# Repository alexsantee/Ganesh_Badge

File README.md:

# Ganesh Badge

The board is entirely based on [Ganesh](https://ganesh.icmc.usp.br/)'s logo, the back side has the logo printed in silkscreen and the front side has a circuit part shaped like the logo, which serves as a ground plane. The front also has the names of our main study areas.

The project is based in the PIC10F200 microcontroler, which offers low cost, decent current sourcing and 4 I/O pins.
The PCB features an LED, header pins intended as a serial and a programming interfaces and a button. These are for creating simple CTF-like challenges yielding a flag, being the button a mean of switching which challenges are currently running.
The lower part of the board has an USB micro-B connector for powering and the top part has a hole intended for easy carrying as a keychain, necklace or even nailing it to a wall.

Mouse bites from [this](https://github.com/madworm/Panelization.pretty) repository.

The PCB was made in KiCAD and intended for low-cost manufacturing at JLCPCB

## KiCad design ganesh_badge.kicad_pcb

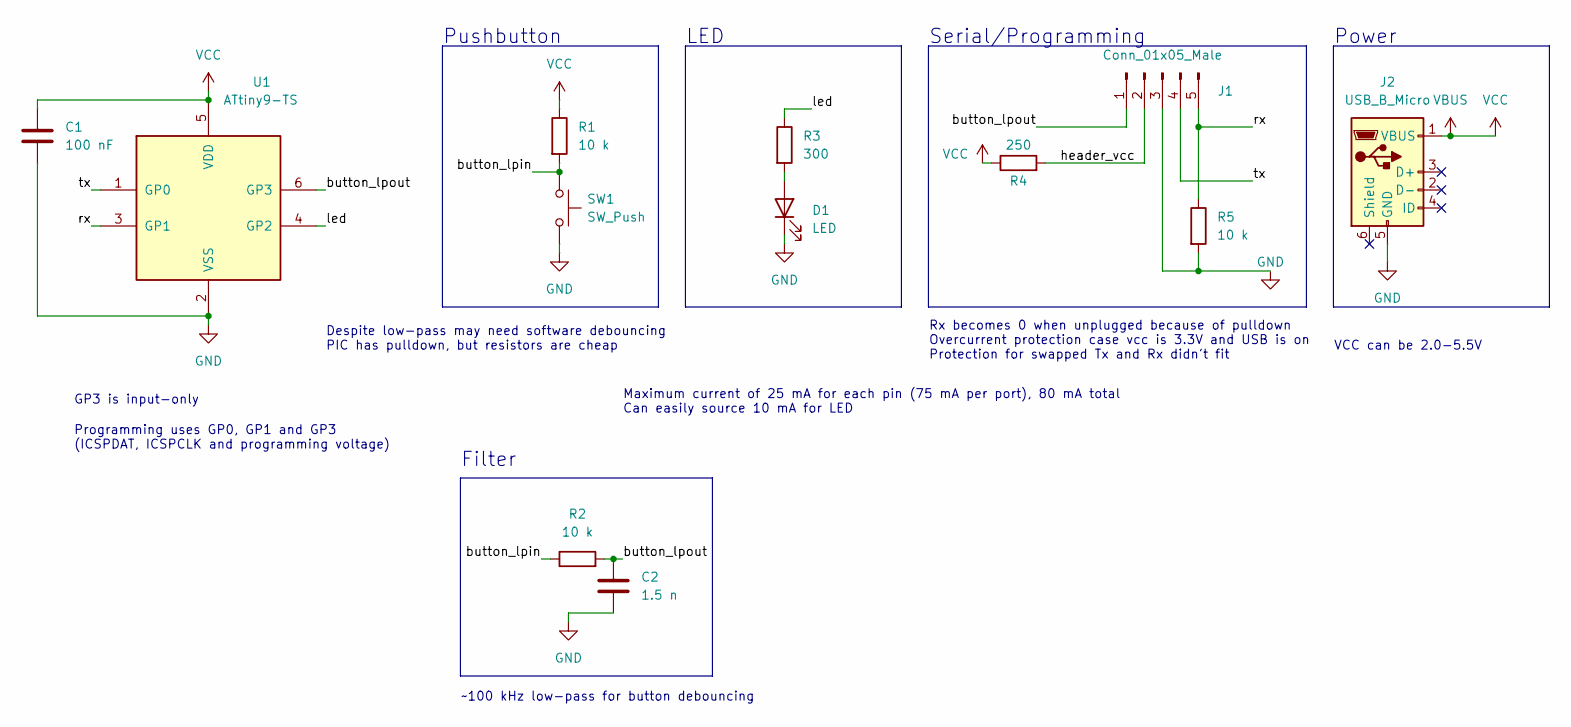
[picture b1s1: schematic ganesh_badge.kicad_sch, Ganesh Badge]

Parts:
C1: 100 nF; C_0603_1608Metric
C2: 1.5 n; C_0603_1608Metric
D1: LED; LED_0603_1608Metric
J1: Conn_01x05_Male; PinHeader_1x05_P2.54mm_Vertical
J2: USB_B_Micro; MicroQTJ_2pads
R1, R2, R5: 10 k; R_0603_1608Metric
R3: 300; R_0603_1608Metric
R4: 250; R_0603_1608Metric
SW1: SW_Push; TS-1187A-B-A-B
U1: ATtiny9-TS; SOT-23-6_narrow

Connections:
/button_lpin: R1.2, R2.1, SW1.1
/button_lpout: C2.1, J1.1, R2.2, U1.6 (GP3)
/header_vcc: J1.2, R4.2
/led: R3.1, U1.4 (GP2)
/rx: J1.5, R5.1, U1.3 (GP1)
/tx: J1.4, U1.1 (GP0)
GND: C1.2, C2.2, D1.1 (K), J1.3, J2.5 (GND), R5.2, SW1.2, U1.2 (VSS)
unnamed: D1.2 (A), R3.2
VBUS: C1.1, J2.1 (VBUS), R1.1, R4.1, U1.5 (VDD)

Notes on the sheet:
Despite low-pass may need software debouncing PIC has pulldown, but resistors are cheap
Maximum current of 25 mA for each pin (75 mA per port), 80 mA total Can easily source 10 mA for LED
Filter
~100 kHz low-pass for button debouncing
Programming uses GP0, GP1 and GP3 (ICSPDAT, ICSPCLK and programming voltage)
Rx becomes 0 when unplugged because of pulldown Overcurrent protection case vcc is 3.3V and USB is on Protection for swapped Tx and Rx didn't fit
Serial/Programming
VCC can be 2.0-5.5V
Pushbutton
Power
LED
GP3 is input-only

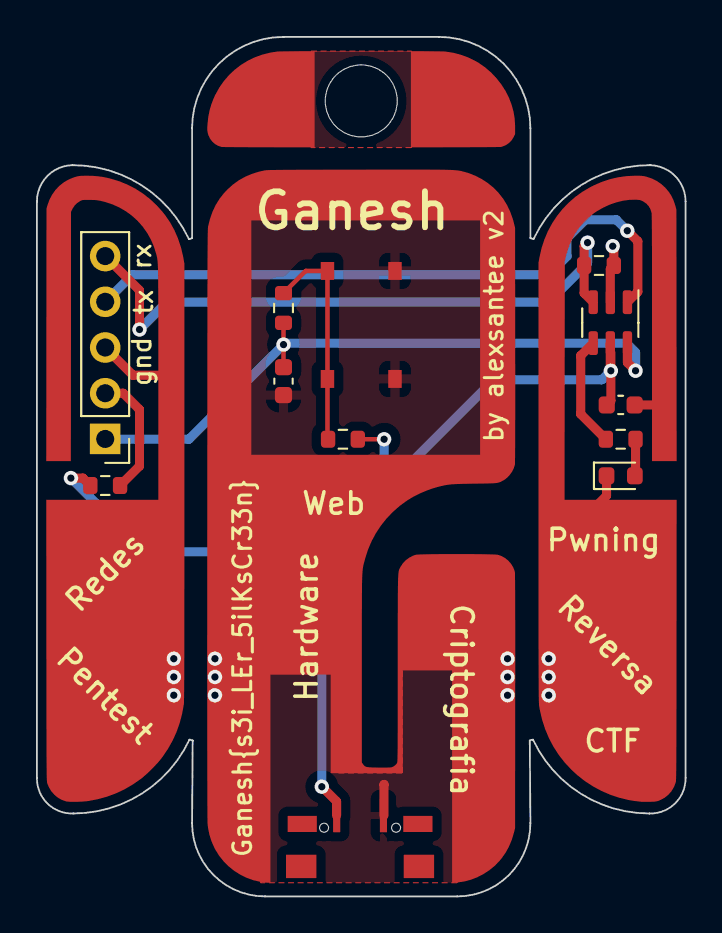
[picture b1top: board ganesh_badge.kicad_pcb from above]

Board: 2 copper layers, 36.0 x 47.8 mm, 15 parts (1 on the bottom side), 9 nets.

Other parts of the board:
Hole: MountingHole_4mm
Logo_silk: LOGO; 35x46_2
logo_cobre: LOGO; 35x46_2-furado

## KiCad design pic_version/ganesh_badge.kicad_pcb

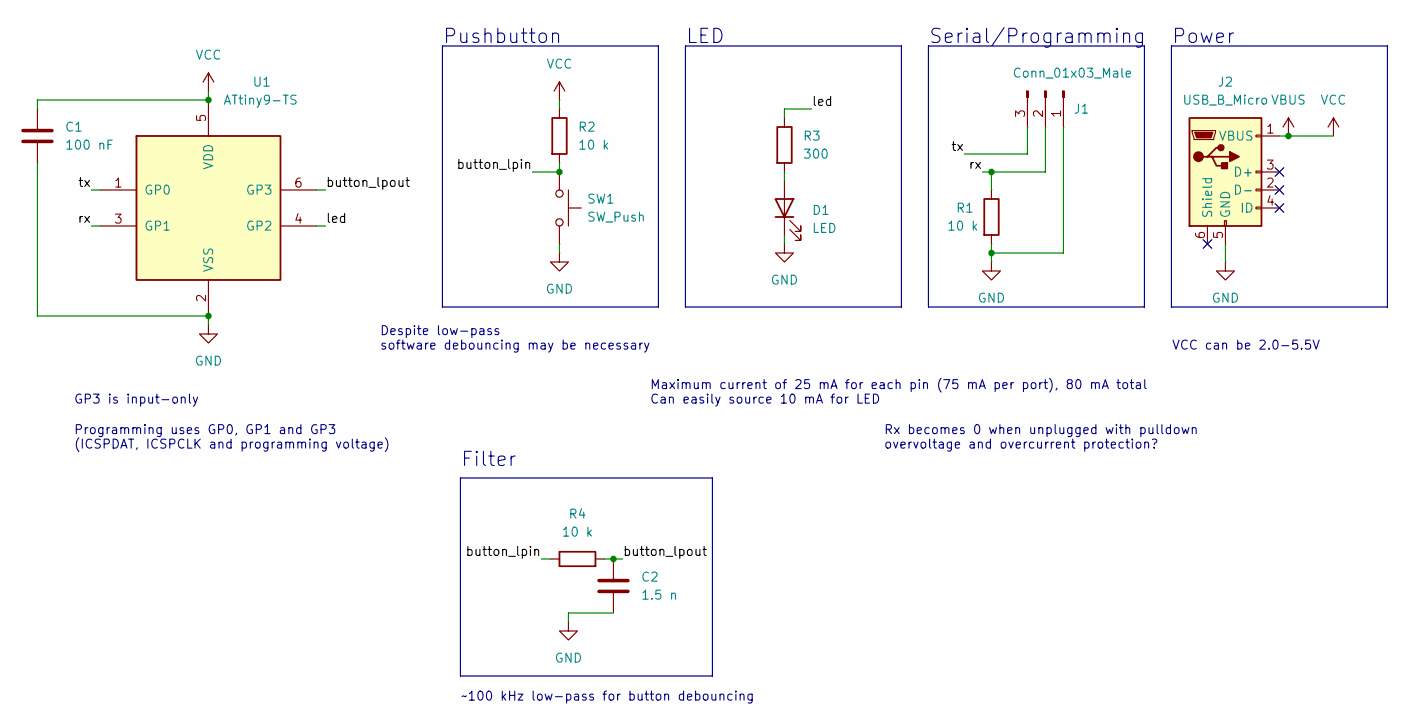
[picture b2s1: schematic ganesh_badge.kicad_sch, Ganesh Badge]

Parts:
C1: 100 nF; C_0603_1608Metric
C2: 1.5 n; C_0603_1608Metric
D1: LED; LED_0603_1608Metric
J1: Conn_01x03_Male; PinHeader_1x03_P2.00mm_Vertical
J2: USB_B_Micro; MicroQTJ_2pads
R1, R2, R4: 10 k; R_0603_1608Metric
R3: 300; R_0603_1608Metric
SW1: SW_Push; TS-1187A-B-A-B
U1: ATtiny9-TS; SOT-23-6_narrow

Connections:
/button_lpin: R2.2, R4.1, SW1.1
/button_lpout: C2.1, R4.2, U1.6 (GP3)
/led: R3.1, U1.4 (GP2)
/rx: J1.2, R1.1, U1.3 (GP1)
/tx: J1.3, U1.1 (GP0)
GND: C1.2, C2.2, D1.1 (K), J1.1, J2.5 (GND), R1.2, SW1.2, U1.2 (VSS)
unnamed: D1.2 (A), R3.2
VBUS: C1.1, J2.1 (VBUS), R2.1, U1.5 (VDD)

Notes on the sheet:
Despite low-pass software debouncing may be necessary
Maximum current of 25 mA for each pin (75 mA per port), 80 mA total Can easily source 10 mA for LED
Filter
~100 kHz low-pass for button debouncing
Programming uses GP0, GP1 and GP3 (ICSPDAT, ICSPCLK and programming voltage)
Rx becomes 0 when unplugged with pulldown overvoltage and overcurrent protection?
Serial/Programming
VCC can be 2.0-5.5V
Pushbutton
Power
LED
GP3 is input-only

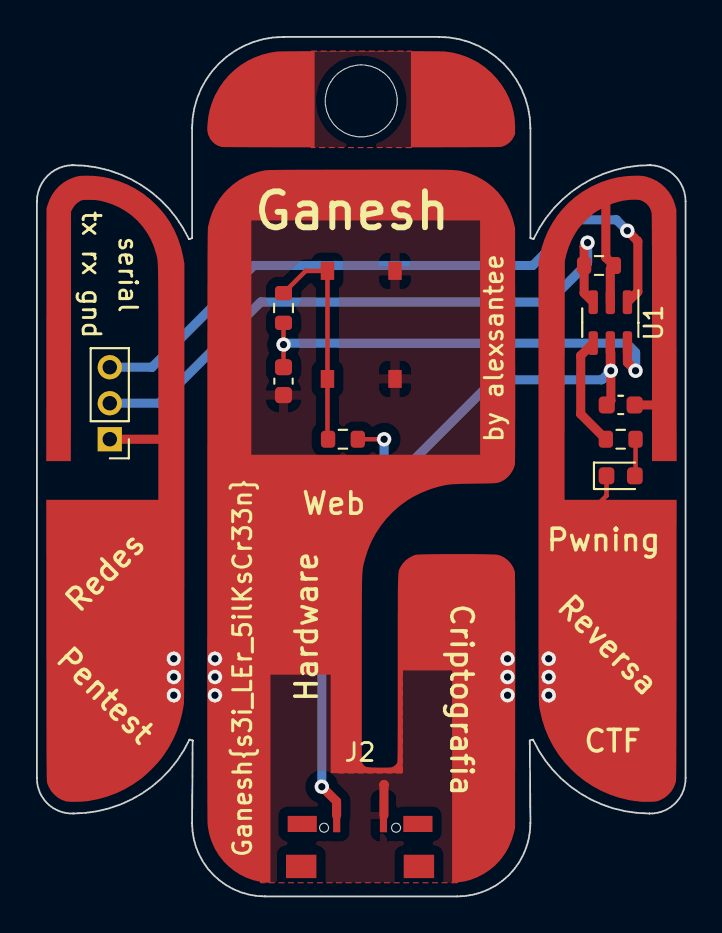
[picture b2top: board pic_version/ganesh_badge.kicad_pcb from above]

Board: 2 copper layers, 36.0 x 47.8 mm, 14 parts (1 on the bottom side), 8 nets.

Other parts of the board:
Hole: MountingHole_4mm
Logo_silk: LOGO; 35x46_2
logo_cobre: LOGO; 35x46_2-furado

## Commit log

2022-09-28 first design
2022-09-28 readme image fix
2022-10-17 created PIC10 version
2022-10-26 initial firmware development
2022-11-20 finished firmware
2023-01-10 simple text fixes
2023-01-10 Clears memory for real device
2023-01-10 panelization fixes
2023-01-10 changed 3d view to picture of actual board
2023-01-10 image downscaling
2023-02-22 changes pic_version to main version and discards attiny
2023-02-22 removes acidentally added file
2023-02-22 changed header to be more compatible with pickit3
2023-02-27 added ground plane to back layer for aesthetics and better EMI
2024-01-06 Added Ganesh's website to readme
